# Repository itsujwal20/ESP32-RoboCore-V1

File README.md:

# ESP32-RoboCore V1

A custom-designed 4-layer development board based on the **ESP32-WROOM-32** SoC, tailored for robotics applications and modular sensor interfacing. This board includes onboard voltage regulation, USB-UART communication, and multiple headers for I²C, PWM, and more.

---

## 🧩 Features

- **Microcontroller:** ESP32-WROOM-32
- **Power Supply:**
  - 12V Barrel Jack input
  - LM2596S-5 (5V regulator)
  - AMS1117-3.3 (3.3V LDO regulator)
- **USB-UART:** CH340C IC with USB-C support
- **Modular Headers:**
  - I²C Header
  - PWM Header
  - MPU6050 IMU Header
  - OLED Display Header
- **Push Buttons:** 2 x Tactile switches
- **3.3V & 5V Rails**
- **PCB Type:** 4-layer custom PCB
- **Keep-Out Zone:** Defined for onboard ESP32 antenna

---

## 🖼️ Images

| PCB Preview | Circuit Diagram |
|-------------|------------------|
|  |  |

| 3D Front View | 3D Back View |
|---------------|---------------|
|  |  |

---

## 📁 Project Structure
```
ESP32-RoboCore-V1/
├── ESP32-RoboCore V1.kicad_pcb # PCB layout
├── ESP32-RoboCore V1.kicad_sch # Schematic
├── ESP32-RoboCore V1.kicad_pro # KiCad project file
├── Gerber Files/ # Gerber files for fabrication
├── Images/ # Preview images
│ ├── 3D-Back.png
│ ├── 3D-Front.png
│ ├── Circuit.png
│ └── PCB.png
└── README.md
```

---

## 📦 Gerber Files

The production-ready Gerber files are available in the `Gerber Files/` directory. These files were generated using **KiCad** and are ready to be uploaded to any PCB fabrication service (e.g., JLCPCB, PCBWay, etc.).

---

## 📚 Tools Used

- **Schematic & PCB Design:** KiCad
- **3D Model Rendering:** KiCad 3D Viewer
- **Microcontroller:** ESP32-WROOM-32

---

## 👨‍💻 Author

**Ujwal Kumar S**  
Electronics and Electrical Engineering  
[GitHub Profile](https://github.com/itsujwal20)

---

## ⚙️ License

This project is open-source under the [MIT License](LICENSE).

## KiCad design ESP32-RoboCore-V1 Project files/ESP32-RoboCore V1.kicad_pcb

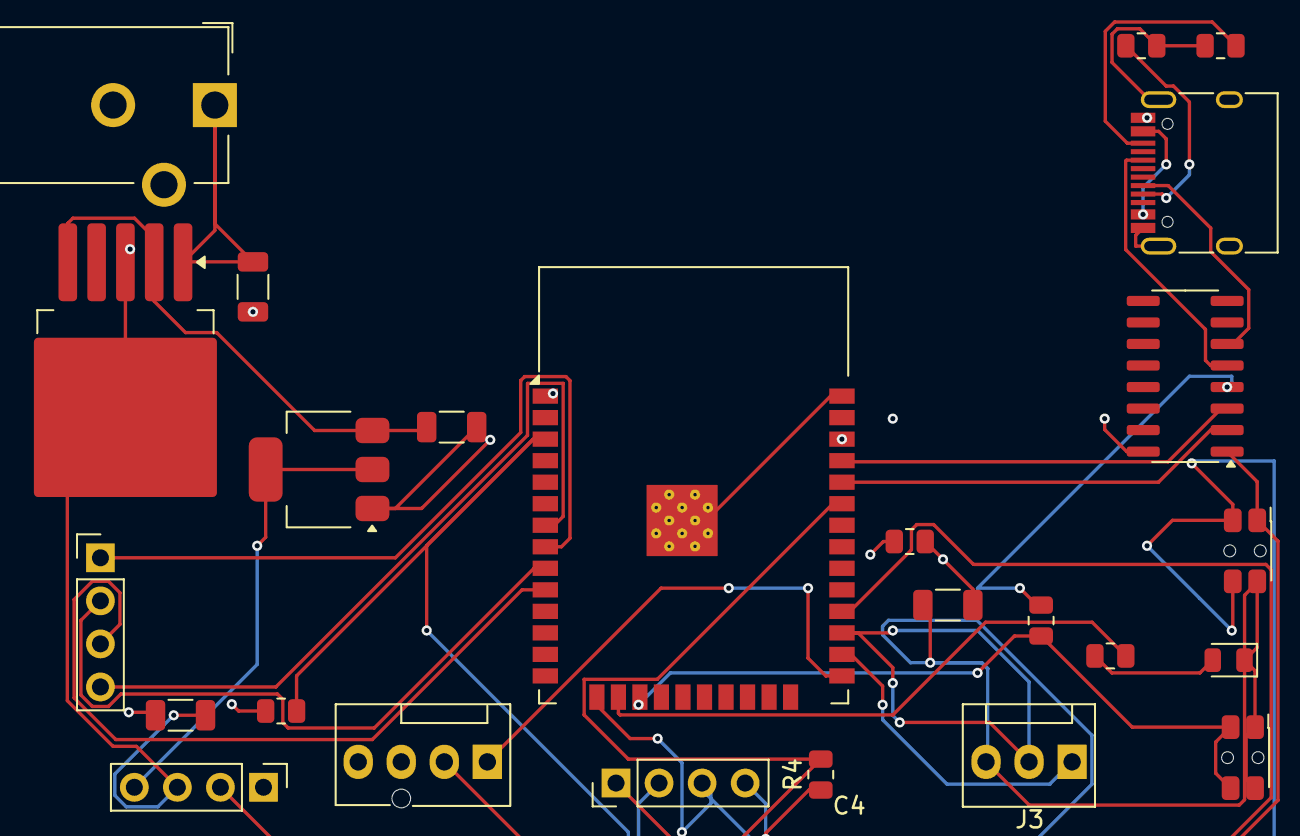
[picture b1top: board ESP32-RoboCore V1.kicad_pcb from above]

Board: 4 copper layers, 25 parts (0 on the bottom side), 25 nets.

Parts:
C1, C2, C3: 10uF; C_1206_3216Metric
C4: 0.1uF; C_1206_3216Metric
D2: LED; LED_0805_2012Metric
J1: USB_C; USB_C_Receptacle_HRO_TYPE-C-31-M-12
J2: Barrel_Jack; BarrelJack_CUI_PJ-102AH_Horizontal
J3: UART; FanPinHeader_1x03_P2.54mm_Vertical
J4: I2C HEADDER; FanPinHeader_1x04_P2.54mm_Vertical
J5: PWM HEADER; PinHeader_1x04_P2.54mm_Vertical
J6: OLED_HDR; PinHeader_1x04_P2.54mm_Vertical
J7: MPU6050 Header; PinHeader_1x04_P2.54mm_Vertical
R1: 10k; R_0805_2012Metric
R2, R3: 330; R_0805_2012Metric
R4, R5: 4.7k; R_0805_2012Metric
R6, R7: 5.1k; R_0805_2012Metric
SW1, SW2: SW_Push; SW_SPST_EVQP7C
U1: ESP32-WROOM-32
U2: AMS1117-3.3; SOT-223-3_TabPin2
U3: LM2596S-5; TO-263-5_TabPin3
U4: CH340C; SOIC-16_3.9x9.9mm_P1.27mm

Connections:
/+3.3v: C3.1, C4.2, J4.4, J6.4, J7.4, R1.1, R3.1, R4.1, R5.1, U2.2 (VO), U4.4 (V3)
/+5v: C2.1, U2.3 (VI), U3.2 (OUT), U3.5 (~ON/OFF)
/IO1: U1.35 (TXD0/IO1), U4.3 (RXD)
/IO3: U1.34 (RXD0/IO3), U4.2 (TXD)
/IO21: J6.1, J7.1, R4.2, U1.33 (IO21)
/IO22: J6.2, J7.2, R5.2, U1.36 (IO22)
GND: C1.2, C2.2, C3.2, C4.1, D2.1 (K), J1.A1 (GND), J1.A12 (GND), J1.B1 (GND), J1.B12 (GND), J1.S1 (SHIELD), J2.2, J3.3, J4.3, J6.3, J7.3, R6.1, R7.1, SW1.1, SW2.1, U1.1 (GND), U1.15 (GND), U1.38 (GND), U1.39 (GND), U2.1 (GND), U3.3 (GND), U4.1 (GND)
unnamed: D2.2 (A), R2.1
unnamed: J1.A5 (CC1), R6.2
unnamed: J1.B5 (CC2), R7.2
unnamed: J3.1, U1.26 (IO4)
unnamed: J3.2, U1.27 (IO16)
unnamed: J4.1, U1.25 (IO0)
unnamed: J4.2, U1.28 (IO17)
unnamed: J5.1, U1.8 (IO32)
unnamed: J5.2, U1.9 (IO33)
unnamed: J5.3, U1.10 (IO25)
unnamed: J5.4, U1.7 (IO35)
unnamed: R1.2, SW1.2, U1.3 (EN)
unnamed: R2.2, U1.16 (IO13)
unnamed: R3.2, SW2.2, U1.17 (SHD/SD2)
unnamed: C1.1, J2.1, U3.1 (VIN)
unnamed: J1.B6 (D+), U4.5 (UD+)
unnamed: J1.B7 (D-), U4.6 (UD-)
unnamed: J1.A4 (VBUS), J1.A9 (VBUS), J1.B4 (VBUS), J1.B9 (VBUS), U4.16 (VCC)
